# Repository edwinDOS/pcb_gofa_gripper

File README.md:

# pcb_gofa_gripper
This repository contains the PCB design for the ABB GOFA Gripper at UC3M

Desarrollado con:

Application: KiCad x64 on x64

Version: 9.0.1, release build

Libraries:
	wxWidgets 3.2.6
	FreeType 2.13.3
	HarfBuzz 10.2.0
	FontConfig 2.15.0
	libcurl/8.11.1-DEV Schannel zlib/1.3.1

Platform: Windows 10 (compilación 19045), edición de 64 bits, 64 bit, Little endian, wxMSW

Build Info:
	Date: Mar 30 2025 01:11:30
	wxWidgets: 3.2.6 (wchar_t,wx containers)
	Boost: 1.86.0
	OCC: 7.8.1
	Curl: 8.11.1-DEV
	ngspice: 44
	Compiler: Visual C++ 1942 without C++ ABI
	KICAD_IPC_API=ON

Locale: 
	Lang: es_ES
	Enc: UTF-8
	Num: 1.234,5
	Encoded кΩ丈: D0BACEA9E4B888 (sys), D0BACEA9E4B888 (utf8)

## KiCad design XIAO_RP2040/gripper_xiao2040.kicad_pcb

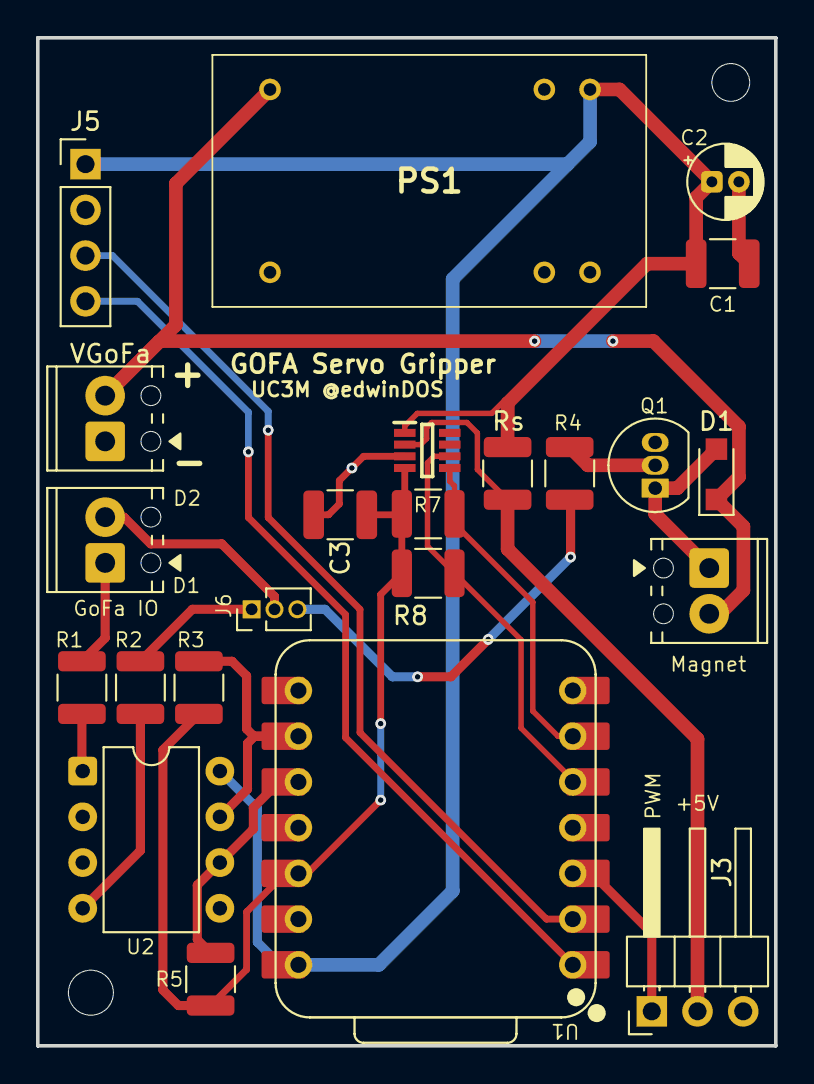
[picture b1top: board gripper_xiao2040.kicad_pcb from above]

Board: 2 copper layers, 41.0 x 56.0 mm, 23 parts (0 on the bottom side), 20 nets.

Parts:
C1: 100n; C_1210_3225Metric
C2: 10uF; CP_Radial_D4.0mm_P1.50mm
C3: C; C_1210_3225Metric
D1: 1N4148; Nexperia_CFP3_SOD-123W
IC1: INA236BIDDFR; SOT65P280X110-8N
J1: GoFa IO; TerminalBlock_Phoenix_MPT-0,5-2-2.54_1x02_P2.54mm_Horizontal
J2: VGoFa; TerminalBlock_Phoenix_MPT-0,5-2-2.54_1x02_P2.54mm_Horizontal
J3: Servo; PinHeader_1x03_P2.54mm_Horizontal
J4: Magnet; TerminalBlock_Phoenix_MPT-0,5-2-2.54_1x02_P2.54mm_Horizontal
J5: Conn_01x04; PinHeader_1x04_P2.54mm_Vertical
J6: Jumper; PinHeader_1x03_P1.27mm_Vertical
PS1: TEL_8-2411; TEL82411
Q1: BC237; TO-92_Inline
R1, R2, R3, R5, R7, R8: R; R_1210_3225Metric
R4: 4K7; R_1210_3225Metric
Rs: R; R_1210_3225Metric
U1: XIAO-RP2040-DIP
U2: HCPL-2631; DIP-8_W7.62mm

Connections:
+5V: C1.1, C2.1, IC1.1 (IN+), J5.1, PS1.9 (+VOUT), Rs.2, U1.14 (VBUS), U2.8 (VCC)
/+3V: C3.2, IC1.4 (VS), R3.1, R5.1, R7.2, R8.1, U1.12 (3V3)
/A0: J5.4, U1.1 (GPIO26/ADC0/A0)
/D2: J5.3, U1.2 (GPIO27/ADC1/A1)
/DO1: J1.1, R1.1
/DO2: J1.2, J6.2
/PWM: J3.1, U1.3 (GPIO28/ADC2/A2)
/SCL: IC1.5 (SCL), R7.1, U1.6 (GPIO7/SCL)
/SDA: IC1.6 (SDA), R8.2, U1.5 (GPIO6/SDA)
/VGoFa: D1.1 (K), J2.2, J4.2, PS1.16 (+VIN_(VCC))
/Vsensed: IC1.2 (IN-), J3.2, Rs.1
/do1_coupled: R3.2, U1.9 (GPIO2/SCK), U2.7 (VO1)
/do2_coupled: R5.2, U1.10 (GPIO4/MISO), U2.6 (VO2)
GND: C1.2, C2.2, C3.1, IC1.3 (GND), J2.1, J3.3, J5.2, PS1.1 (-VIN_(GND)), PS1.10 (-VOUT), Q1.3 (E), U1.13 (GND), U2.2 (C1), U2.3 (C2), U2.5 (GND)
unnamed: D1.2 (A), J4.1, Q1.1 (C)
unnamed: J6.1, R2.2
unnamed: J6.3, R4.1
unnamed: Q1.2 (B), R4.2
unnamed: R1.2, U2.1 (A1)
unnamed: R2.1, U2.4 (A2)

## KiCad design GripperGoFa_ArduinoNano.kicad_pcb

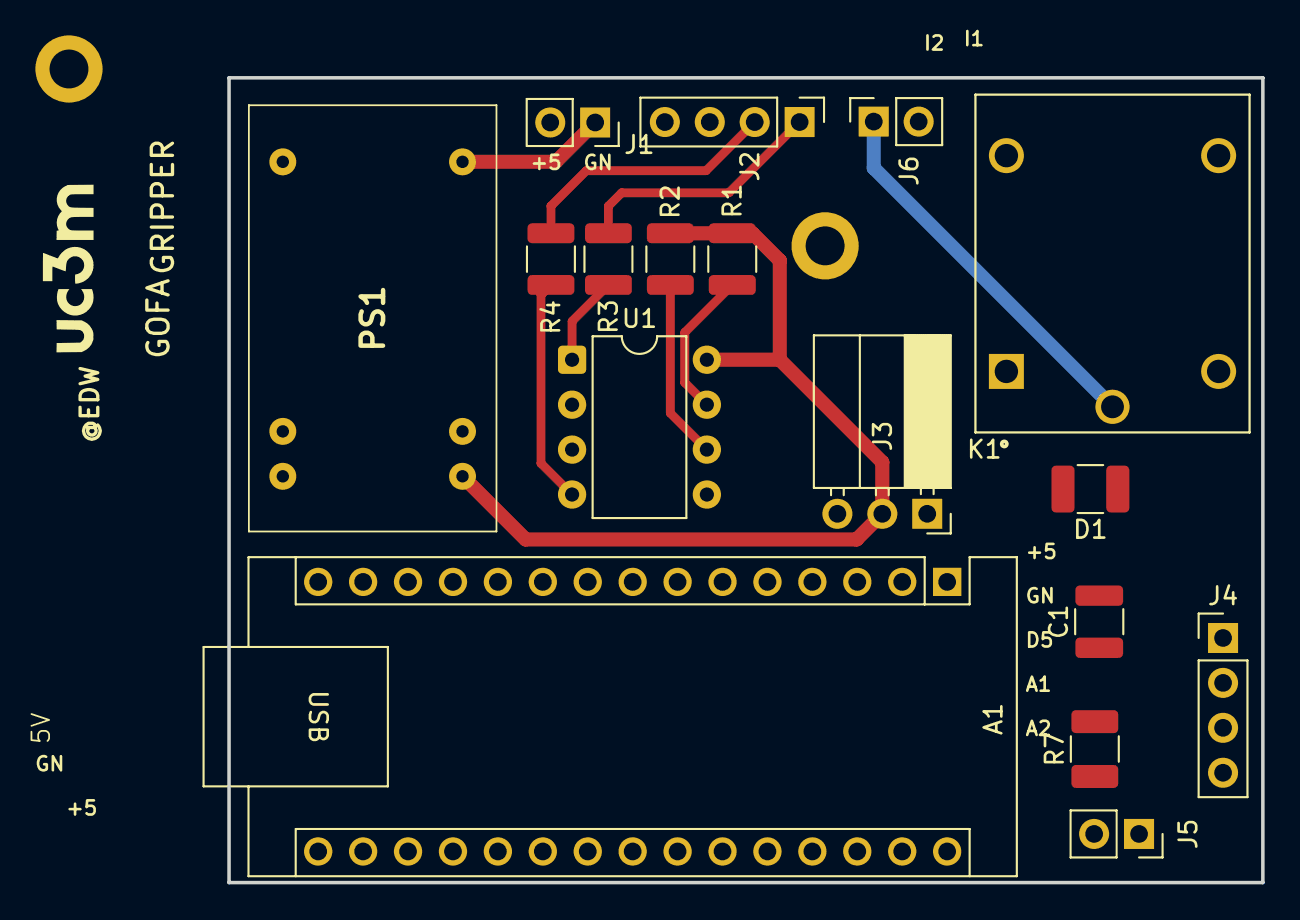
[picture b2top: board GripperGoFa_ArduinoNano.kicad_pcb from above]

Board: 2 copper layers, 58.5 x 45.5 mm, 20 parts (0 on the bottom side), 16 nets.

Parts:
A1: Arduino_Nano_Every; Arduino_Nano
C1: C; C_1210_3225Metric
D1: D; R_1210_3225Metric_Pad1.30x2.65mm_HandSolder
G: LOGO
H2: MountingHole; MountingHole_2.2mm_M2_DIN965_Pad
H2#2: MountingHole_2.2mm_M2_DIN965_Pad
J1: VCC; PinSocket_1x02_P2.54mm_Vertical
J2: Input; PinHeader_1x04_P2.54mm_Vertical
J3: Servo; PinSocket_1x03_P2.54mm_Horizontal
J4: OptSensor; PinHeader_1x04_P2.54mm_Vertical
J5: FSR; PinSocket_1x02_P2.54mm_Vertical
J6: Magnet; PinSocket_1x02_P2.54mm_Vertical
K1: SRD-05VDC-SL-C; RELAY_SRD-05VDC-SL-C
PS1: TEL_8-2411; TEL82411
R1, R2: 10k; R_1210_3225Metric
R3, R4: 2k7; R_1210_3225Metric
R7: R; R_1210_3225Metric_Pad1.30x2.65mm_HandSolder
U1: HCPL-2631; DIP-8_W7.62mm

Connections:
+5V: A1.27 (+5V), C1.1, J3.2, J4.1, J5.1, PS1.9 (+VOUT), R1.1, R2.1, U1.8 (VCC)
+24V: D1.2 (A), J1.1, PS1.16 (+VIN_(VCC))
/D5: A1.8 (D5), J4.3
/DI1: A1.5 (D2), R1.2, U1.7 (VO1)
/DI2: A1.6 (D3), R2.2, U1.6 (VO2)
/MagnetDO: A1.10 (D7), K1.A1
/PWM: A1.12 (D9), J3.1
GND: A1.4 (GND), A1.29 (GND), C1.2, J1.2, J3.3, J4.2, J6.2, K1.A2, PS1.1 (-VIN_(GND)), PS1.10 (-VOUT), R7.2, U1.2 (C1), U1.3 (C2), U1.5 (GND)
unnamed: A1.20 (A1), J4.4
unnamed: A1.21 (A2), J5.2, R7.1
unnamed: D1.1 (K), K1.NO
unnamed: J2.1, R3.1
unnamed: J2.2, R4.1
unnamed: J6.1, K1.COM
unnamed: R3.2, U1.1 (A1)
unnamed: R4.2, U1.4 (A2)

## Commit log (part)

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2025-09-19 first version of gripper pcb for Arduino Nano
2025-10-16 Readme updated
2025-10-22 update components
2025-10-22 test changes
2025-10-22 test2 changes
2026-02-19 GitIgnore updated
2026-02-19 New PCB version based on XIAO-RP2040
2026-02-20 Improving PCB routing and including Arduino code
2026-02-20 adding XIAO pinout
